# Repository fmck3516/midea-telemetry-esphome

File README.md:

# midea-telemetry-esphome

An [ESPHome](https://esphome.io/) component to feed test-port telemetry from Midea mini-splits and centrally ducted units into Home Assistant. No Home Assistant? It works standalone too: the dongle serves its own web dashboard and JSON API, with an optional InfluxDB + Grafana stack for long-term history.

It supports a variety of brands including MRCOOL, Cooper&Hunter, Pioneer, and Senville.

## Support

Please use [GitHub Issues](https://github.com/fmck3516/midea-telemetry-esphome/issues) for bug reports and feature requests. 
For questions and general discussion, join the [Home Assistant Community thread](https://community.home-assistant.io/t/1015912). I'm active there.

## Compatibility

The dongle has been tested successfully with the following outdoor units:

| Brand | Outdoor Models | Type | 
|---|---|---|
| MRCOOL | DIY-12-HP-C-115C25 | single-zone mini-split |
| Cooper&Hunter | CH-HPR06F9-230VO, CH-N36LCU-230VO | single-zone mini-split |
| Senville | SENDC-36-HF-OG | centrally ducted unit |
| Pioneer | YN018GMFI20RPD | single-zone mini-split |
| ACiQ | ES-48Z-M6C | multi-zone mini-split |

Since Midea-made mini-splits and centrally ducted units are very similar across brands, many other units from brands like MRCOOL, Cooper&Hunter, Senville, Pioneer, Blueridge, etc. are supported as well. To confirm, look for a test port (a 4-pin JST connector labeled `TEST`) on your unit's wiring diagram or on the outdoor unit's control or auxiliary board.

**Multi-zone units:** the dongle runs on multi-zone systems, but four sensors (T1, T2, TT, Pr) have come back empty on the ACiQ multi-zone unit.

## Hardware

All you need is a **dual-core ESP32** and a level shifter. A dual core is required because the bus bit-banging runs in a dedicated FreeRTOS task. A full request/response cycle keeps the bus busy for ~380 ms, far too long to run on the main loop.

Recommended hardware:
- [XIAO ESP32S3](https://www.amazon.com/dp/B0BYSB66S5)
- [3.3V–5V Level Shifter](https://www.amazon.com/dp/B07F7W91LC)

I used the following connector kits, but you can get away with a single 4-pin male JST-XH connector:
- [XH 2.54mm Connector Kit](https://www.amazon.com/dp/B08G18PWQ6)
- [2.54mm Connector 4 Pin Male Adapter Right Angle](https://www.amazon.com/dp/B0BMDQLR4Q)

### PCB & Enclosure

The KiCad project, schematic, and Gerber files live in [pcb/](pcb/) - a 2-layer board, 41.5 × 22 mm, 1.6 mm thick, with four M2 mounting holes. You solder in just three parts - the ODU connector, the level-shifter module, and the XIAO - and that's the whole build. FreeCAD sources plus STL and 3MF exports for the 3D-printable enclosure are in [enclosure/](enclosure/).

| PCB (top)  | PCB (bottom)  |
| --- | --- |
|  |  |

| Assembled dongle | Enclosure |
| --- | --- |
|  |  |

I've added a jumper that ties the test port's +5V to the XIAO's 5V pin. Use the jumper to run the board straight off the ODU with no USB cable. Leave it off if the board is connected to USB. I also recommend the use of a USB isolator since ground on the test port is not referenced to earth.

## Safety

The outdoor unit runs on mains voltage, and internal capacitors can retain a dangerous charge after being unplugged. Always

- turn off the breaker,
- pull the disconnect, and
- wait several minutes and/or verify capacitors are discharged

before performing the installation. Wear appropriate PPE. Consult a qualified electrician when in doubt.

## Installation

*(See [Safety](#safety) first if you're jumping straight to this section.)*

Remove the top panel of the ODU. You'll see the control board. Remove the screws securing the control board to the ODU, then detach the cables from the cable clamps so you can lift the board for access — there's no need to unplug the cables themselves. The test port on my units is located at the front of the board. Plug in the dongle, with the red wire facing toward you. Reattach the cables to the cable clamps and secure the board back to the ODU. There should be enough clearance to tuck the dongle into the service panel — this lets you access the dongle later without needing to remove the control board again. Reinstall the top panel.

| Control board | Test port |
| --- | --- |
|  |  |

| Dongle plugged in | Dongle tucked into service panel |
| --- | --- |
|  |  |

For a visual walkthrough, see [this installation video](https://www.youtube.com/watch?v=poEmSZnrnjs).

## First use

Upon first start, the dongle brings up a temporary WiFi hotspot so you can connect it to your WiFi network. Join the `midea-telemetry-esphome` network (password `midea-telemetry-esphome`) and provide your WiFi network's SSID and password in the popup that appears. Once connected, the dongle serves a webserver at `http://midea-telemetry.local` (useful if you don't run Home Assistant), and Home Assistant automatically detects it as a new ESPHome device.

| WiFi hotspot | WiFi setup |
| --- | --- |
|  |  |

| On-board webserver | Home Assistant auto-discovery |
| --- | --- |
|  |  |

## Configuration

See [example_midea_telemetry.yaml](example_midea_telemetry.yaml) for a complete configuration with every supported sensor. That file uses a local `components:` source, so it's flashable straight from a checkout of this repo; to pull the component remotely instead, switch the source to `github://fmck3516/midea-telemetry-esphome`.

## Flashing

Flash your ESP32 with `esphome`. On macOS:

```sh
brew install esphome
esphome run example_midea_telemetry.yaml
```

## Supported Sensors

The following sensors are currently supported. `Code` is the two-letter parameter code the Midea
service manuals use for the same value, so a reading here can be matched against the one the unit
shows on its own diagnostic display; `—` means the manuals define no code for that value.

| Code | Name | Unit |
|---|---|---|
| TT | `indoor_setpoint` | °C |
| T1 | `indoor_ambient_temperature` | °C |
| T2 | `indoor_coil_temperature` | °C |
| T3 | `outdoor_coil_temperature` | °C |
| T4 | `outdoor_ambient_temperature` | °C |
| TP | `discharge_temperature` | °C |
| — | `ipm_temperature` | °C |
| — | `operating_mode` | raw |
| oT | `compressor_frequency_indoor_target` | Hz |
| FT | `compressor_frequency_outdoor_target` | Hz |
| Fr | `compressor_frequency_actual_int` | Hz |
| Fr | `compressor_frequency_actual_float` | Hz |
| — | `compressor_frequency_outdoor_control` | Hz |
| Pr | `outdoor_fan_speed` | RPM |
| Lr | `eev_steps` | raw |
| dL | `current_draw` | A |
| Ac | `input_voltage` | V |
| Uo | `dc_bus_voltage` | V |
| — | `error_code_1` | bit mask for `E3, E0, P8, Eb, P6, PA, L3, L0` |
| — | `error_code_2` | bit mask for `E60, E61, L2, E2, E1, L1, P90, P91` |
| — | `error_code_3` | bit mask for `E80, E81, E1, E83, P0, P1, E5, P8` |
| — | `error_code_4` | bit mask for `P4, P6, PA, L5, L3, L2, E7` |

[FRAME-BYTES.md](FRAME-BYTES.md) documents each sensor in great detail.

## JSON endpoint

Add `expose_json_endpoint: true` to serve all mapped sensors and the underlying raw data as JSON. It needs the `web_server` component:

```yaml
web_server:
  port: 80

midea_telemetry:
  clk_pin: GPIO3
  dat_pin: GPIO2
  expose_json_endpoint: true
```

The endpoint is served at `/json` (e.g. `http://midea-telemetry.local/json`), independent of Home Assistant. This is useful for reverse engineering, scripting, and for using the device without Home Assistant.

## Frame log

Add `log_frames: true` to log every request sent to the ODU and every response received. The lines show up in the ESPHome dashboard's log view (and in `esphome logs`):

```yaml
midea_telemetry:
  clk_pin: GPIO3
  dat_pin: GPIO2
  log_frames: true
```

```
[17:56:13][D][midea_telemetry:300]: tx=AA000000000000000056
[17:56:13][D][midea_telemetry:319]: rx=55006D457671401F03B0   checksum ok
[17:56:14][D][midea_telemetry:300]: tx=AA010000000000000055
[17:56:14][D][midea_telemetry:319]: rx=55016D457671401F03B0   checksum error
[17:56:14][D][midea_telemetry:300]: tx=AA020000000000FF0055
[17:56:14][D][midea_telemetry:316]: rx=                       no response
```

Each response is tagged `checksum ok`, `checksum error`, `bad header` (checksum fine, but not a `0x55` frame of a known type), or `no response` (the ODU didn't answer, so the request is retried). The lines are logged at DEBUG, the logger's default level; if you've set `logger: level:` to `INFO` or lower, they won't appear. Leave the option off when you're not using it: it adds about five log lines per second.

## Long-term history (InfluxDB + Grafana)

For a permanent, Home-Assistant-independent history, [`influxdb-grafana/`](influxdb-grafana/) provides a ready-to-run Docker stack: Telegraf polls each dongle's `/json` endpoint and stores the raw frame bytes in InfluxDB v2, and Grafana decodes them into a provisioned dashboard. See [influxdb-grafana/README.md](influxdb-grafana/README.md).

## Prior Art

I've documented the test-port protocol in great detail on Medium: [Reverse Engineering Midea's ODU Diagnostic Port](https://medium.com/@florian.mckee/reverse-engineering-mideas-odu-diagnostic-port-af603e159053). The firmware in this repository is based on those findings. Start there if you want to understand the protocol; the byte mappings and conversion formulas in the [Supported Sensors](#supported-sensors) table come straight from it.

## Warranty

This is a hobby project. I've permanently installed the telemetry module on all of my units without any problems. That said, use it at your own risk. I do not assume any liability if it causes damage to your equipment. See [LICENSE](LICENSE) for additional information.

## Disclaimer

Midea is a trademark of Midea Group. This is an independent, unofficial hobby project and is not affiliated with, authorized, endorsed by, or sponsored by Midea. The name is used only to describe which hardware the project interoperates with. All product names and trademarks are the property of their respective owners.

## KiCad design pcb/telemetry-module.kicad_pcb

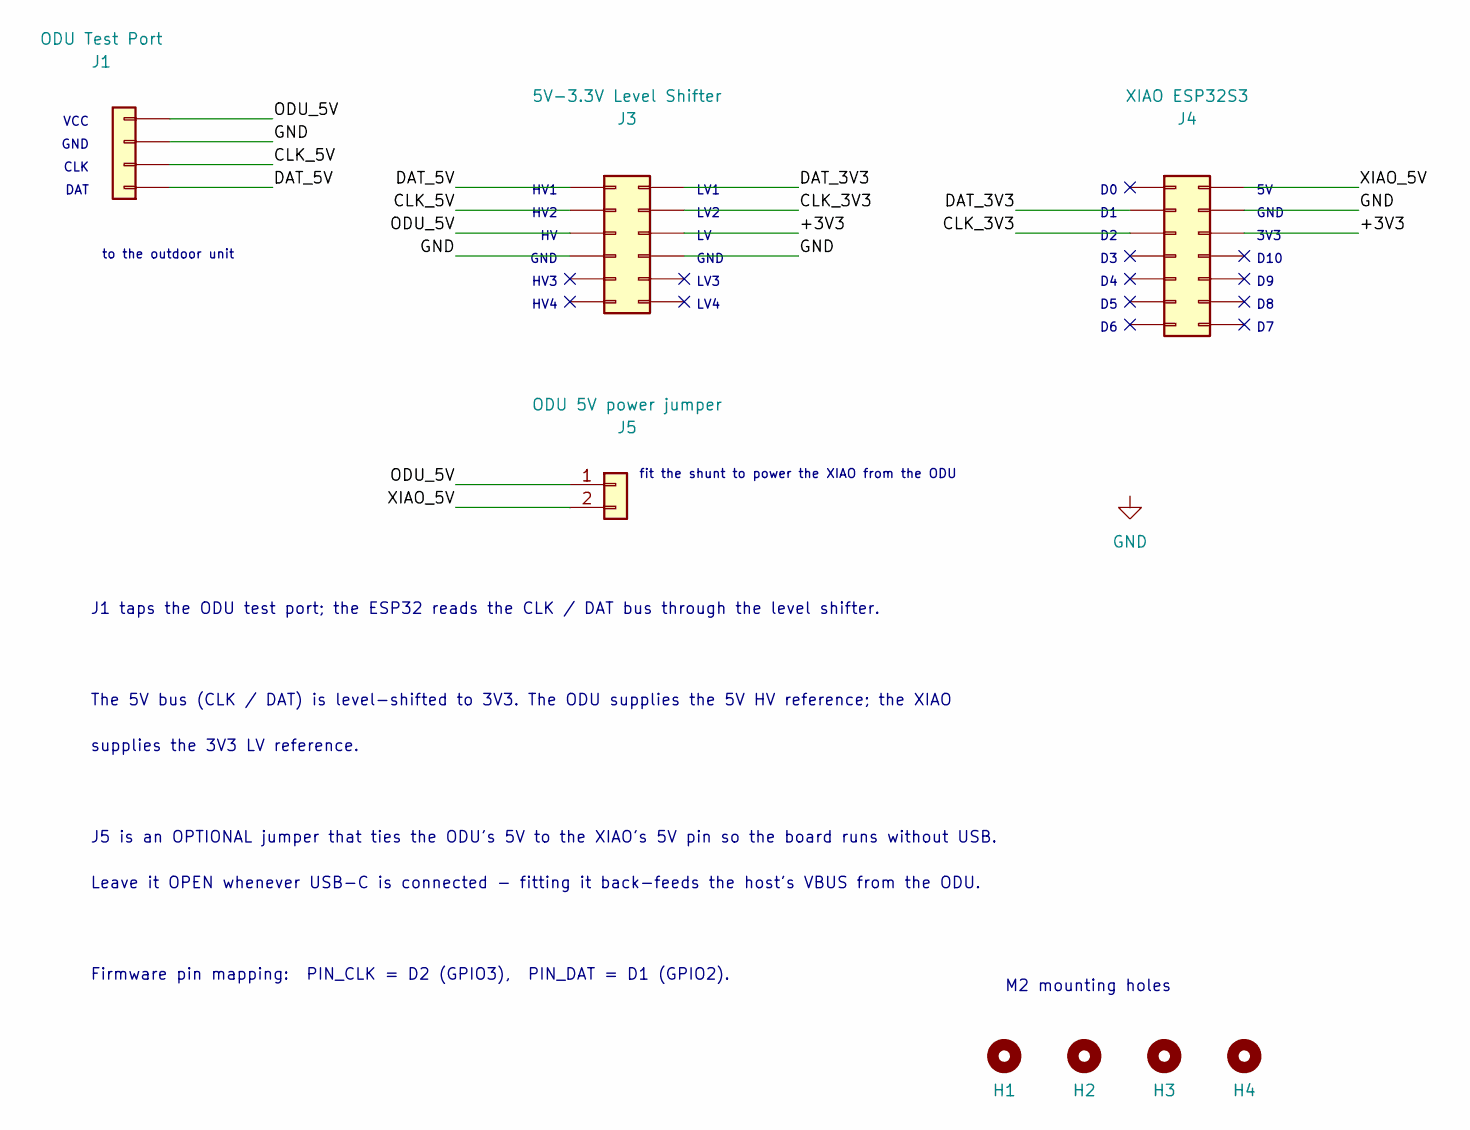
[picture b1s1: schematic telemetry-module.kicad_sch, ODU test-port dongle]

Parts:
H1, H2, H3, H4: MountingHole; MountingHole_2.2mm_M2
J1: ODU Test Port; JST_XH_B4B-XH-A_1x04_P2.50mm_Vertical
J3: 5V-3.3V Level Shifter; Module_LevelShifter_4ch_2x06_P2.54mm_RM10.16
J4: XIAO ESP32S3; Module_Seeed_XIAO_2x07_P2.54mm_RM15.24
J5: ODU 5V power jumper; PinHeader_1x02_P2.54mm_Vertical

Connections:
/+3V3: J3.6, J4.12
/CLK_3V3: J3.4, J4.3
/CLK_5V: J1.2, J3.3
/DAT_3V3: J3.2, J4.2
/DAT_5V: J1.1, J3.1
/ODU_5V: J1.4, J3.5, J5.1
/XIAO_5V: J4.14, J5.2
GND: J1.3, J3.7, J3.8, J4.13

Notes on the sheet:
to the outdoor unit
GND
CLK
fit the shunt to power the XIAO from the ODU
Leave it OPEN whenever USB-C is connected - fitting it back-feeds the host's VBUS from the ODU.
HV3
J1 taps the ODU test port; the ESP32 reads the CLK / DAT bus through the level shifter.
HV1
The 5V bus (CLK / DAT) is level-shifted to 3V3. The ODU supplies the 5V HV reference; the XIAO
HV4
DAT
M2 mounting holes
supplies the 3V3 LV reference.
LV3
LV4
3V3
VCC
LV2
J5 is an OPTIONAL jumper that ties the ODU's 5V to the XIAO's 5V pin so the board runs without USB.
D10
LV1
HV2
Firmware pin mapping: PIN_CLK = D2 (GPIO3), PIN_DAT = D1 (GPIO2).

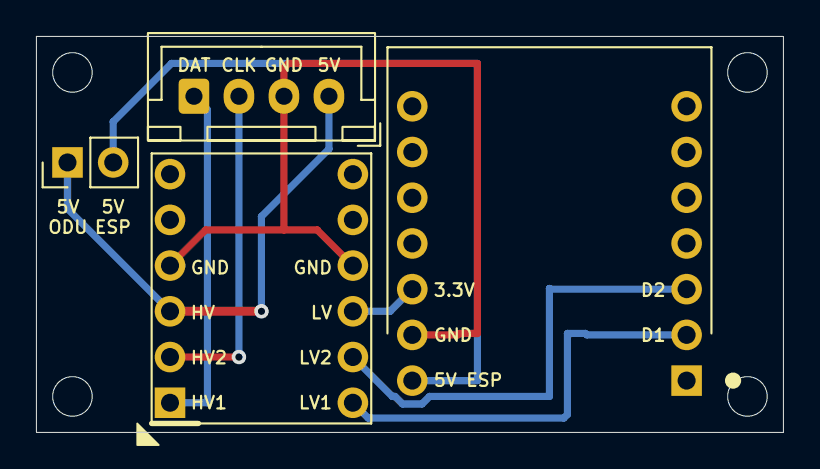
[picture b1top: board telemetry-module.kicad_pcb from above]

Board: 2 copper layers, 41.5 x 22.0 mm, 8 parts (0 on the bottom side), 8 nets.
